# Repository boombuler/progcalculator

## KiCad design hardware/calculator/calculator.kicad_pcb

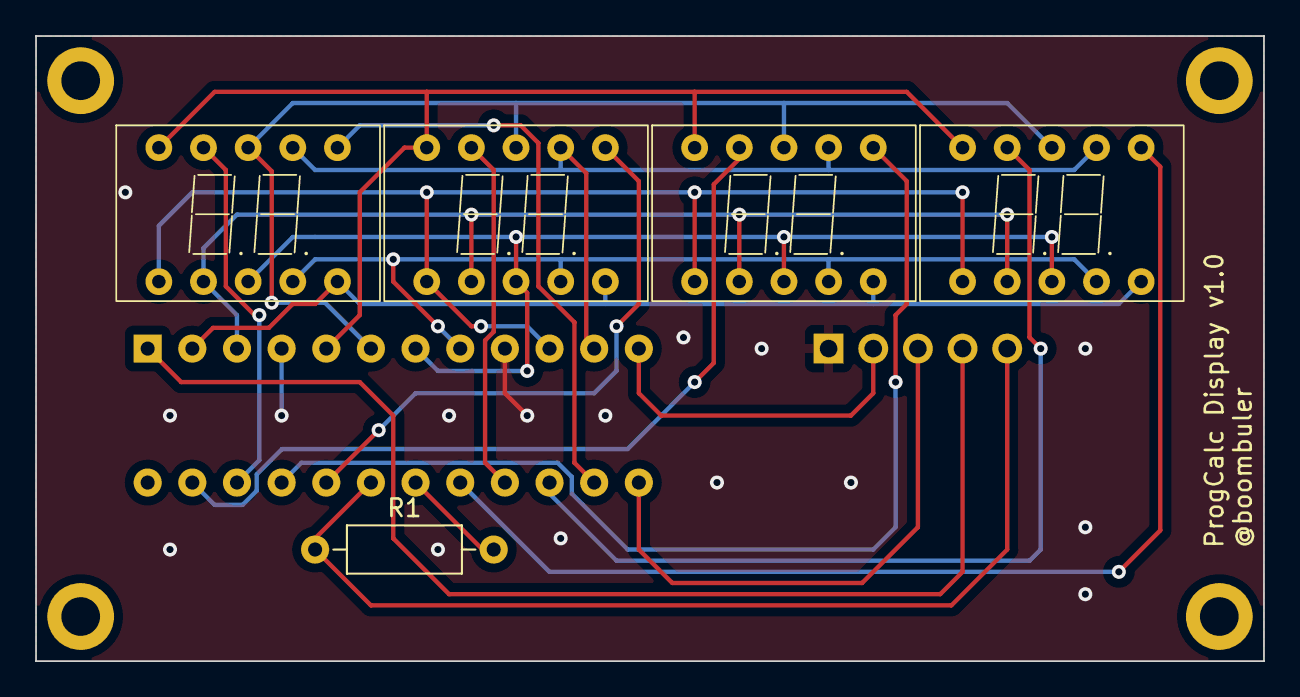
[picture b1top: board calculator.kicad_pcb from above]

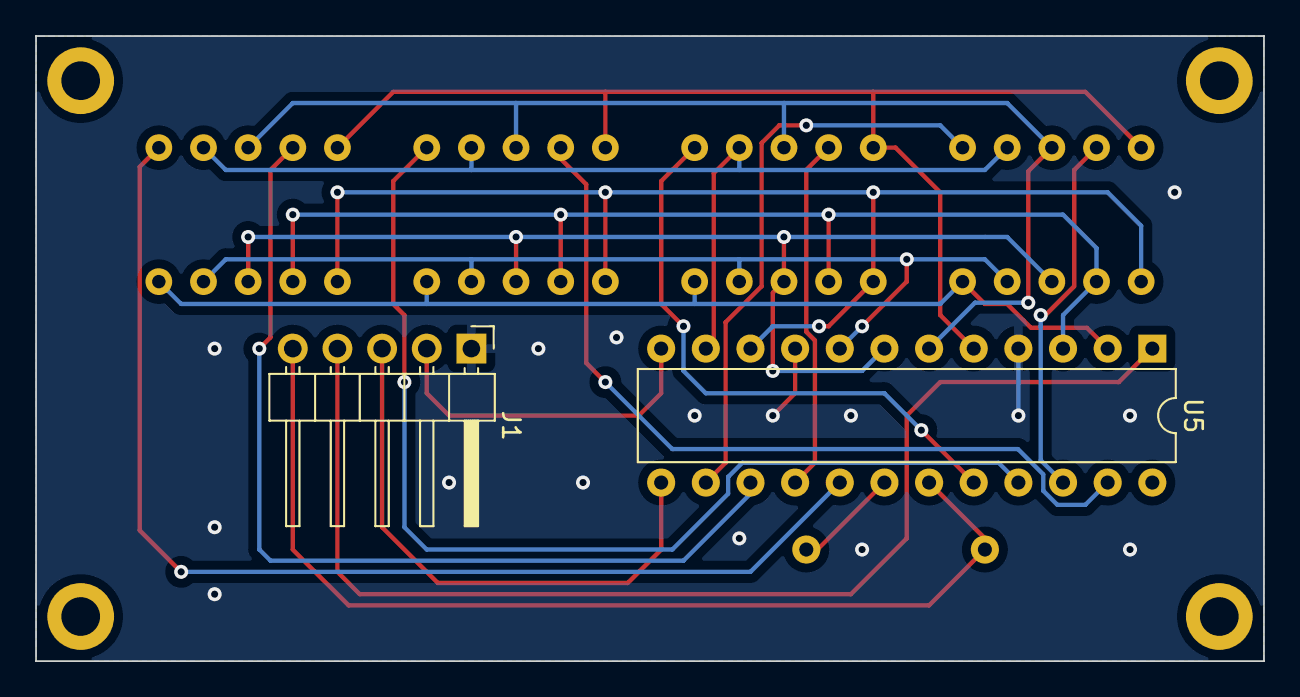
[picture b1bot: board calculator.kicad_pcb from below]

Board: 2 copper layers, 69.8 x 35.6 mm, 7 parts (2 on the bottom side), 22 nets.

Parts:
J1: Conn_01x05; PinHeader_1x05_P2.54mm_Horizontal
R1: 30k; R_Axial_DIN0207_L6.3mm_D2.5mm_P10.16mm_Horizontal
U5: MAX7219; DIP-24_W7.62mm
U6, U7, U8, U9: 2821BS

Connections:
+5V: J1.5, R1.1, U5.19 (V+)
/Display/DSP_H_CLK: J1.3, U5.13 (CLK)
/Display/DSP_H_CS: J1.2, U5.12 (LOAD)
/Display/DSP_H_MOSI: J1.4, U5.1 (DIN)
/Display/Dig1: U5.22 (SEG_DP), U6.9 (DIG1)
/Display/Dig2: U5.14 (SEG_A), U6.6 (DIG2)
/Display/Dig3: U5.16 (SEG_B), U7.9 (DIG1)
/Display/Dig4: U5.20 (SEG_C), U7.6 (DIG2)
/Display/Dig5: U5.23 (SEG_D), U8.9 (DIG1)
/Display/Dig6: U5.21 (SEG_E), U8.6 (DIG2)
/Display/Dig7: U5.15 (SEG_F), U9.9 (DIG1)
/Display/Dig8: U5.17 (SEG_G), U9.6 (DIG2)
GND: J1.1, U5.4 (GND), U5.9 (GND)
unnamed: U5.2 (DIG_0), U6.5 (DP), U7.5 (DP), U8.5 (DP), U9.5 (DP)
unnamed: U5.11 (DIG_1), U6.7 (A), U7.7 (A), U8.7 (A), U9.7 (A)
unnamed: U5.6 (DIG_2), U6.8 (B), U7.8 (B), U8.8 (B), U9.8 (B)
unnamed: U5.7 (DIG_3), U6.3 (C), U7.3 (C), U8.3 (C), U9.3 (C)
unnamed: U5.3 (DIG_4), U6.2 (D), U7.2 (D), U8.2 (D), U9.2 (D)
unnamed: U5.10 (DIG_5), U6.1 (E), U7.1 (E), U8.1 (E), U9.1 (E)
unnamed: U5.5 (DIG_6), U6.10 (F), U7.10 (F), U8.10 (F), U9.10 (F)
unnamed: U5.8 (DIG_7), U6.4 (G), U7.4 (G), U8.4 (G), U9.4 (G)
unnamed: R1.2, U5.18 (ISET)

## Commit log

2024-02-11 Added License
2024-02-12 Add first bit of hardware schema
2024-02-17 Added display pcb
2024-02-25 Added code to controll the display module
2024-08-02 Ported Main Hardware to ATmega328P Since the STL is missing by default for arduino and `ArduinoSTL` does not implement all required templates some changes were needed.
2024-08-05 Added hardware implementation and unit tests
2024-08-05 Added test for initial state
2024-08-06 moved calculation to shunting yard algorithm
    This way it partial results can be calculated early on and less memory is used.
2024-08-07 fixed number reuse
    If you don't enter a new number before the operator, the displayed number should be reused.
2024-08-07 Added more tests.
2024-08-26 Added Keyboard Layout Also implemented debug output
2024-08-26 Added unit test for calculation reset
2024-08-26 Updated Display Commands
    Some letters have changed ignore casing. That way the text is readable if the casing of the letters does not have a valid representation.
2024-08-26 Added debouncing for mode selection
